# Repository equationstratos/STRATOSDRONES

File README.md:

# STRATOSDRONES

**A fully open-source DJI Tello EDU class drone** — hardware (KiCad PCB you can order assembled from JLCPCB), 3D-printable frame (OpenSCAD), flight firmware (ESP32-P4 + ESP32-C6), Tello SDK 2.0 wire-compatible programming interface, swarming, and a complete Gazebo simulation that speaks the exact same protocol as the real drone.

> Fly your mission scripts against the Gazebo sim today, order the PCB, print the frame, and run the *same unmodified Python code* on the real drone.

## Specs vs DJI Tello EDU

| | DJI Tello EDU | STRATOSDRONES |
|---|---|---|
| Weight / wheelbase | 87 g / 118 mm | ~92 g / 118 mm |
| Motors / props | brushed 8520 / 3" | identical (Tello-compatible props) |
| MCU | proprietary + Myriad 2 | **ESP32-P4** (flight + camera + H.264 hw encoder) + **ESP32-C6** (Wi-Fi 6) |
| Sensors | IMU, baro, ToF, optical flow | ICM-42688-P, SPL06-001, VL53L1X, PMW3901 |
| Camera | 5 MP, 720p30 H.264 | **OV5647 5 MP MIPI-CSI, hardware H.264 720p30 (Tello wire format) + 1080p30 extension** |
| SDK | Tello SDK 2.0 (UDP 8889/8890/11111) | **wire-compatible incl. video** — [djitellopy](https://github.com/damiafuentes/DJITelloPy) works unmodified — plus extensions |
| Swarm | STA mode on shared AP | identical, **plus simulated swarms in Gazebo** |
| Simulation | none | full Gazebo Harmonic model running the *same* flight-control code |
| License | closed | MIT (code), CERN-OHL-P-2.0 (hardware), CC-BY-4.0 (docs) |

## Repository layout

```
fc_core/            Platform-independent flight control core (pure C99, no RTOS deps)
                    — compiled into BOTH the ESP32-P4 firmware and the Gazebo plugin
firmware/           ESP-IDF project for ESP32-P4 (esp32p4 target)
sim/                Gazebo Harmonic plugin, drone SDF model, worlds, swarm launcher
sim/viz/            Self-contained 3-D drone viewer (open drone_viewer.html) generated from the SDF
sdk/python/         stratospy: thin djitellopy add-on for STRATOS extensions + examples
android/            Android ground-control app (Tello SDK 2.0 client — takeoff/land/flip, joysticks, live video)
fr4n6/              Fr4n6-001 — the 5" brushless FPV-class model (charter, CAD, hardware plan; same fc_core)
foldable/           Fr4n7-F — folding-arm variant (spring pivots + latch; button or `deploy`-servo release; CAD + animated viewer)
fpv85/              Fr4n8-001 — outdoor micro FPV, 85 mm class (ELRS radio + analog 5.8G video, 2S brushless; CAD + viewer + playground sim)
fpv2/               Fr4n9-001 — outdoor 2" FPV, 98 mm (same design language + SAME shared AIO board as fpv85)
TinyHoopMK1/        Fr4n10-001 — programmable/swarm 2.5" FPV (JeNo Pocket V2 frame, clean-room): 4 modes (manual/stabilized/program/swarm), ELRS + LoRa 868 fleet link, flow+ToF position hold, analog or DJI O4 Lite video
hardware/pcb/       KiCad project + JLCPCB fab outputs (gerbers, BOM, CPL) + component map
hardware/pcb_fpv/   STRATOS FPV AIO — shared brushless 2S board for fpv85+fpv2 (design.py → CI-generated KiCad board)
hardware/pcb_tinyhoop/ STRATOS TINYHOOP AIO — the TinyHoop MK1 board (FPV AIO + flow/ToF + SX1262 LoRa + GPS, 2S-3S)
sdk/lora_dongle/    ground LoRa dongle (ESP32+SX1262) — transparent fc_lorap bridge for the no-Wi-Fi PC/fleet link
hardware/frame/     Parametric OpenSCAD frames → STL:
                      • frame.scad …        open racing-style X-frame
                      • tello_style/ …      closed Tello-size clamshell body
docs/               Build guide, bring-up, SDK reference, architecture, safety
oasis30/            OASIS 30 — 3" build on the Sub250 OasisFly30 frame: parametric
                    gmsh-OCC model (STEP + printable STL), the printed parts the kit
                    lacks, 3-D viewer + assembly simulator
atelier/            FPV build-workshop site + print posters (buy-the-drone option, FPV league)
```

## Quick start (simulation)

```bash
# Ubuntu 24.04 — install Gazebo Harmonic (see docs/build_guide.md), then:
cd sim && cmake -B build && cmake --build build
./spawn_swarm.sh 1                      # one simulated drone on 127.0.0.2

pip install djitellopy
python sdk/python/examples/01_hover.py  # takeoff → hover → land, via the Tello protocol
python sdk/python/examples/03_swarm.py  # ./spawn_swarm.sh 3 first
```

## Status

- [x] `fc_core` flight control core + host tests (ctest, closed-loop SIL)
- [x] Gazebo Harmonic model + plugin, Tello-protocol UDP endpoint, multi-drone
- [x] Python SDK layer + examples
- [x] KiCad PCB + JLCPCB fab package *(review in KiCad before ordering — see docs/build_guide.md)*
- [x] OpenSCAD frame → STL
- [x] ESP32-P4 firmware tree (flight task, drivers, SDK server, H.264 video)
- [x] TinyHoop MK1 (Fr4n10): 4-mode manager + show/figure executor + CRSF + LoRa protocol in `fc_core` (host-tested); DShot/CRSF/SX1262/LoRa firmware (CI-compiled); STRATOS TINYHOOP AIO board; clean-room JeNo Pocket V2 CAD (STL+DXF); `stratospy.lora` + choreography compiler
- [ ] Hardware bring-up (waiting on first PCB batch — see docs/bringup.md)
- [ ] Real-world flight tuning, camera pipeline validation, 2-drone swarm

## Safety

This is a flying machine with spinning propellers. Read `docs/safety.md` before the first
flight: prop guards on, props off for the first power-up, never hand-catch, lipo handling.

## Licenses

- Code (fc_core, firmware, sim, sdk): [MIT](LICENSE)
- Hardware (hardware/): [CERN-OHL-P-2.0](LICENSES/CERN-OHL-P-2.0.txt)
- Documentation (docs/): [CC-BY-4.0](LICENSES/CC-BY-4.0.txt)

Clean-room policy: Crazyflie / ESP-Drone / Betaflight are used as *algorithmic references
only* (papers, datasheets, published behavior). No GPL code is copied. See CONTRIBUTING.md.

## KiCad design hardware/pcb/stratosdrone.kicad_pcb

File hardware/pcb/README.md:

# STRATOSDRONE PCB

A 4-layer, **36×70 mm Tello-style portrait** controller board for the
STRATOSDRONE: chip-down ESP32-P4 (flight + camera + hardware H.264) with an
ESP32-C6-MINI-1 Wi-Fi co-processor, IMU / barometer / ToF / optical-flow
sensors, a MIPI-CSI camera FFC at the nose, 1S USB-C charging at the rear, and
four corner brushed-motor drivers. It drops into the printed body pod
(`../frame/tello_style/`).

**Lost among the parts?** See the annotated component map (`make map`):

**See the board populated in 3-D** — open [`viz/pcb3d_viewer.html`](viz/) (one
offline file, double-click). It synthesises a clean 3-D body for every one of the
115 components straight from the placement data, so the board renders fully
populated **without needing KiCad's 3-D models** (which aren't installed here).
Top / bottom / copper / silkscreen / logo, hover to inspect any part. See
[`viz/README.md`](viz/README.md).

> **Read [`KNOWN_GAPS.md`](KNOWN_GAPS.md) before ordering.** This design is
> generated as a reviewable starting point: the netlist, BOM and placement are
> complete and self-consistent, but signal routing and several datasheet-level
> verifications must be finished by hand in KiCad first.

## Design as code

The board is generated from one source of truth, `scripts/design.py`
(components, LCSC parts, pin-level nets, placement). Regenerate everything:

```bash
make            # board + pinmap + fab + consistency check
make board      # stratosdrone.kicad_pcb from design.py
make pinmap     # firmware/components/board/include/board_pinmap.h
make fab        # jlcpcb/bom.csv, cpl.csv, gerbers/ (preliminary)
make check      # assert board nets + firmware pinmap match design.py
make preview    # preview/top.svg, bottom.svg
```

Requires KiCad 7 (`pcbnew` Python module + `kicad-cli`). The vendored
Espressif P4/C6 symbols and footprints in `lib/` were downgraded to the
KiCad 7 file format; `lib/strat.pretty/` holds project-specific footprints.

## Files

```
stratosdrone.kicad_pcb   generated board (open in KiCad to route)
scripts/design.py        ← edit this; the authoritative netlist + BOM
scripts/gen_pcb.py       design.py -> .kicad_pcb (place, net, pour)
scripts/gen_pinmap.py    design.py -> firmware board_pinmap.h
scripts/export_fab.py    -> jlcpcb/{bom.csv,cpl.csv,gerbers/}
scripts/check_consistency.py  CI gate: board == design == firmware pinmap
lib/                     vendored Espressif + project footprints/symbols
jlcpcb/                  fabrication outputs (BOM/CPL real; gerbers preliminary)
```

## Ordering at JLCPCB (after routing + review)

1. Finish routing in KiCad, fill zones (**B**), run **DRC** to zero errors.
2. Re-export gerbers/drill from KiCad (Plot) — *not* from `export_fab.py`,
   which exports the unrouted board.
3. PCB options: **4-layer**, 1.6 mm, JLC04161H-7628 stackup (controlled
   impedance for the USB/CSI pairs), 0.5 oz outer / 0.5 oz inner, ENIG finish
   (recommended for the fine-pitch QFN and FFC pads).
4. Assembly: **PCBA**, both sides (top: MCU/power/most parts; bottom: the two
   downward sensors). Upload `jlcpcb/bom.csv` and `jlcpcb/cpl.csv`; they use
   the JLC column format and the LCSC part numbers from `design.py`.
5. Confirm every **VERIFY** item in `KNOWN_GAPS.md` is closed.

## Approx. cost (qty 5, indicative — get a live quote)

| | per board |
|---|---|
| 4-layer PCB + PCBA (qty 5, both sides) | ~$18–28 |
| ICM-42688-P (the expensive line) | ~$10.5 |
| ESP32-P4 + C6 module + flash | ~$9 |
| sensors (baro, ToF, flow) + camera module | ~$11 |
| passives, connectors, FETs, USB-C, regulators | ~$6 |
| **board total** | **~$55–65** |
| + motors (×4), 1S 1100 mAh pack, props, frame filament | ~$25 |

Estimate only — not a quote, and excludes the verification rework above.

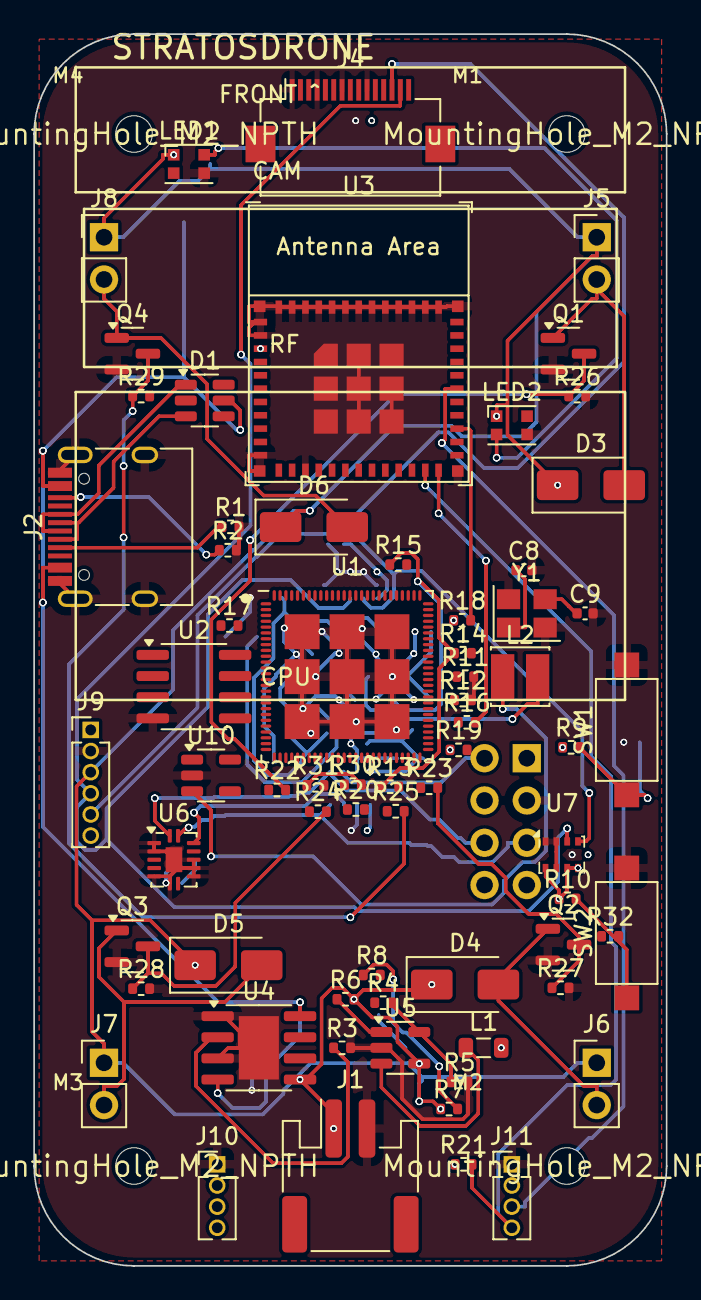
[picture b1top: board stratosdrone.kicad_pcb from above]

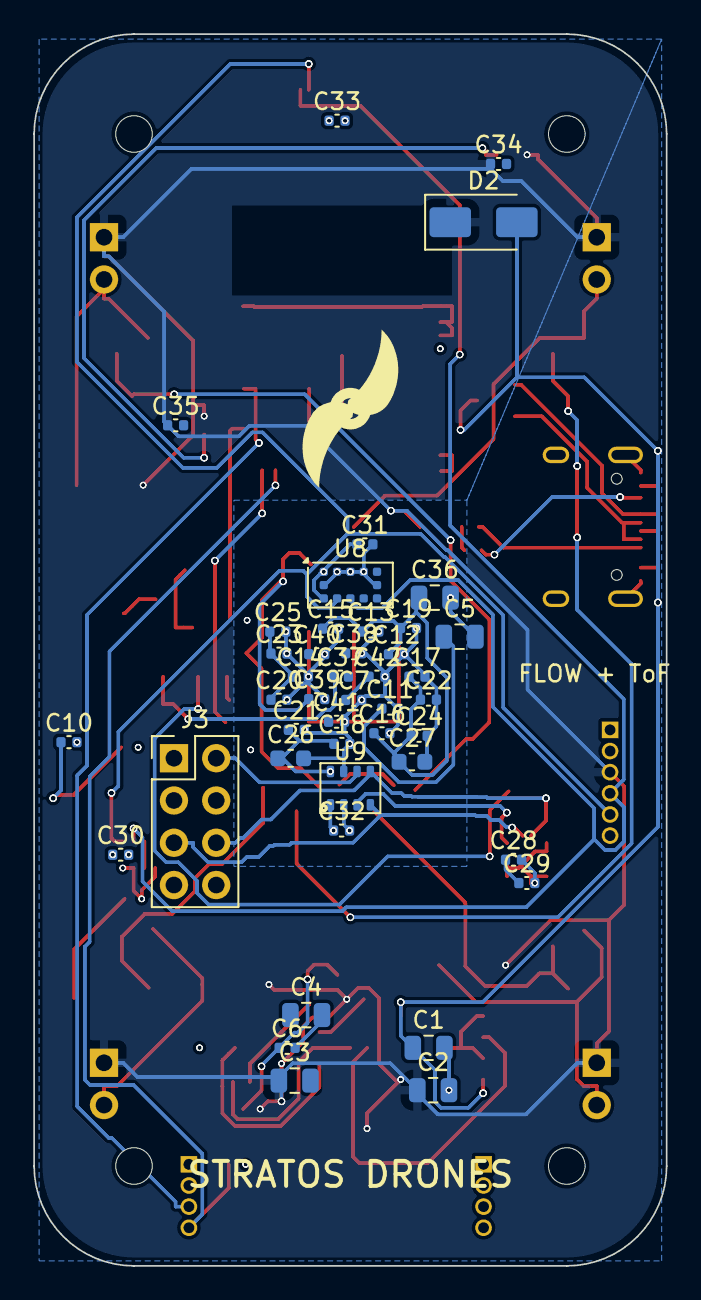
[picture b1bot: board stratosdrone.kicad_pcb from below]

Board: 4 copper layers, 38.0 x 74.0 mm, 116 parts (44 on the bottom side), 78 nets.

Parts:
C1, C2, C3, C36: 10uF; C_0805_2012Metric
C4, C5: 22uF; C_0805_2012Metric
C6, C11, C12, C13, C14, C15, C16, C17, C18, C19, C20, C21, C22, C23, C24, C25, C28, C29, C30, C31, C32, C34, C35, C39, C41, C42: 100nF; C_0402_1005Metric
C7, C10, C33, C38, C40: 1uF; C_0402_1005Metric
C8, C9: 10pF; C_0402_1005Metric
C26, C27: 10uF; C_0603_1608Metric
C37: 20pF; C_0402_1005Metric
D1: USBLC6-2SC6; SOT-23-6
D2: SS34-DNP; D_SMA
D3, D4, D5, D6: SS34; D_SMA
J1: BATT_PH2; JST_PH_S2B-PH-SM4-TB_1x02-1MP_P2.00mm_Horizontal
J2: USB-C-16P; USB_C_Receptacle_HRO_TYPE-C-31-M-12
J3: FLOW_HDR; PinHeader_2x04_P2.54mm_Vertical
J4: CAM_FFC15; Hirose_FH12-15S-0.5SH_1x15-1MP_P0.50mm_Horizontal
J5: MOTOR1; PinHeader_1x02_P2.54mm_Vertical
J6: MOTOR2; PinHeader_1x02_P2.54mm_Vertical
J7: MOTOR3; PinHeader_1x02_P2.54mm_Vertical
J8: MOTOR4; PinHeader_1x02_P2.54mm_Vertical
J9: EXP; PinHeader_1x06_P1.27mm_Vertical
J10: DBG; PinHeader_1x04_P1.27mm_Vertical
J11: C6DBG; PinHeader_1x04_P1.27mm_Vertical
L1: 10uH; L_0805_2012Metric
L2: 2.2uH; L_Cenker_CKCS3015
LED1, LED2: WS2812B-2020; LED_WS2812B-2020_PLCC4_2.0x2.0mm
MH1, MH2, MH3, MH4: MountingHole_M2_NPTH; MountingHole_2.2mm_M2
Q1, Q2, Q3, Q4: AO3400A; SOT-23
R1, R2: 5.1k; R_0402_1005Metric
R3: 1.2k; R_0402_1005Metric
R4, R30, R31: 453k; R_0402_1005Metric
R5, R6, R7, R8, R26, R27, R28, R29: 100k; R_0402_1005Metric
R9, R10, R13, R14, R15, R21, R32: 10k; R_0402_1005Metric
R11, R12: 4.02k; R_0402_1005Metric
R16, R17, R18, R19, R20: 51k; R_0402_1005Metric
R22, R23, R24, R25: 100R; R_0402_1005Metric
SW1: RESET; SW_SPST_CK_RS282G05A3
SW2: BOOT; SW_SPST_CK_RS282G05A3
U1: ESP32-P4NRW32; ESP32-P4
U2: W25Q128JVSIQ; SOIC-8_3.9x4.9mm_P1.27mm
U3: ESP32-C6-MINI-1
U4: TP4056-42-ESOP8; SOIC-8-1EP_3.9x4.9mm_P1.27mm_EP2.41x3.81mm
U5: SY8089AAAC; SOT-23-5
U6: ICM-42688-P; DHVQFN-14-1EP_2.5x3mm_P0.5mm_EP1x1.5mm
U7: SPL06-001; Bosch_LGA-8_2x2.5mm_P0.65mm_ClockwisePinNumbering
U8: VL53L1X; ST_VL53L1x
U9: PMW3901MB; PMW3901MB-TXQT
U10: TLV62569DBVR; SOT-23-5
Y1: 40MHz; Crystal_SMD_3225-4Pin_3.2x2.5mm

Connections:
3V3: C4.1, C12.1, C13.1, C14.1, C15.1, C16.1, C17.1, C18.1, C19.1, C20.1, C21.1, C22.1, C23.1, C24.1, C25.1, C26.1, C27.1, C28.1, C29.1, C30.1, C31.1, C32.1, C33.1, C36.1, J3.1, J3.8, J4.15, J9.1, J10.4, L1.2, R4.1, R9.1, R10.1, R16.1, R17.1, R18.1, R19.1, R20.1, R21.1, R32.1, U1.9, U1.21, U1.51, U1.62, U1.75, U1.77, U1.85, U1.96, U1.101, U1.102, U3.3, U6.5, U6.8, U7.5, U7.6, U7.8, U8.1, U8.11, U9.1, U9.8, U10.4
3V3_EN: R6.1, U5.1
BOOT: R10.2, SW2.1, U1.66
C6_BOOT: J11.4, R21.2, U3.23
C6_EN: U1.98, U3.8
C6_U0RXD: J11.3, U3.30
C6_U0TXD: J11.2, U3.31
CAM_PWDN: J4.11, U1.53
CC1: J2.A5, R1.1
CC2: J2.B5, R2.1
CHIP_PU: C10.1, R9.2, SW1.1, U1.103
CSI_CKN: J4.8, U1.45
CSI_CKP: J4.9, U1.44
CSI_D0N: J4.2, U1.42
CSI_D0P: J4.3, U1.43
CSI_D1N: J4.5, U1.46
CSI_D1P: J4.6, U1.47
CSI_REXT: R11.1, U1.48
CS_FLOW: J3.2, U1.14, U9.6
CS_IMU: U1.13, U6.12
DSI_REXT: R12.1, U1.34
EN_DCDC: U1.79, U10.1
EXP_IO: J9.6, U1.24
FB3V3: R4.2, R5.1, U5.5
FB_DCDC: C37.2, R30.2, R31.1, U1.78, U10.5
FLASH_CK: U1.32, U2.6
FLASH_CS: R13.2, U1.27, U2.1
FLASH_IO0: U1.33, U2.5
FLASH_IO1: U1.28, U2.2
FLASH_IO2: R14.2, U1.29, U2.3
FLASH_IO3: R15.2, U1.31, U2.7
GND: C1.2, C2.2, C3.2, C4.2, C5.2, C6.2, C7.2, C8.2, C9.2, C10.2, C11.2, C12.2, C13.2, C14.2, C15.2, C16.2, C17.2, C18.2, C19.2, C20.2, C21.2, C22.2, C23.2, C24.2, C25.2, C26.2, C27.2, C28.2, C29.2, C30.2, C31.2, C32.2, C33.2, C34.2, C35.2, C36.2, C38.2, C39.2, C40.2, C41.2, C42.2, D1.2, J1.2, J2.A1, J2.A12, J2.B1, J2.B12, J2.S1, J3.3, J3.7, J4.1, J4.4, J4.7, J4.10, J9.2, J10.1, J11.1, LED1.3, LED2.3, Q1.2, Q2.2, Q3.2, Q4.2, R1.2, R2.2, R3.2, R5.2, R8.2, R11.2, R12.2, R26.2, R27.2, R28.2, R29.2, R31.2, SW1.2, SW2.2, U1.105, U2.4, U3.1, U3.2, U3.11, U3.14, U3.36, U3.37, U3.38, U3.39, U3.40, U3.41, U3.42, U3.43, U3.44, U3.45, U3.46, U3.47, U3.48, U3.49, U3.50, U3.51, U3.52, U3.53, U4.1, U4.3, U4.9, U5.2, U6.2, U6.3, U6.6, U6.7, U6.9, U6.10, U6.11, U6.15, U7.1, U7.2, U7.7, U8.2, U8.3, U8.4, U8.6, U8.12, U9.2, U9.7, U10.2, Y1.2, Y1.4
GPIO36_STRAP: R32.2, U1.68
I2C_SCL: J4.13, J9.5, U1.8, U7.4, U8.10
I2C_SDA: J4.14, J9.4, U1.7, U7.3, U8.9
IMU_INT: U1.23, U6.4
LED_D12: LED1.4, LED2.2
LED_DIN: LED1.2, U1.52
M1_D: D3.2, J5.2, Q1.1
M1_G: R22.1, U1.87
M1_GATE: Q1.3, R22.2, R26.1
M2_D: D4.2, J6.2, Q2.1
M2_G: R23.1, U1.88
M2_GATE: Q2.3, R23.2, R27.1
M3_D: D5.2, J7.2, Q3.1
M3_G: R24.1, U1.89
M3_GATE: Q3.3, R24.2, R28.1
M4_D: D6.2, J8.2, Q4.1
M4_G: R25.1, U1.90
M4_GATE: Q4.3, R25.2, R29.1
PROG: R3.1, U4.2
SDIO_CLK: U1.19, U3.25
SDIO_CMD: R16.2, U1.20, U3.24
SDIO_D0: R17.2, U1.15, U3.26
SDIO_D1: R18.2, U1.16, U3.27
SDIO_D2: R19.2, U1.17, U3.28
SDIO_D3: R20.2, U1.18, U3.29
SPI_MISO: J3.6, U1.12, U6.1, U9.5
SPI_MOSI: J3.5, U1.11, U6.14, U9.4
SPI_SCLK: J3.4, U1.10, U6.13, U9.3
SW3V3: L1.1, U5.3
SW_CORE: L2.1, U10.3
U0RXD: J10.3, U1.70
U0TXD: J10.2, U1.69
USB_DM_C: D1.3, J2.A7, J2.B7
USB_DM_MCU: D1.4, U1.49
USB_DP_C: D1.1, J2.A6, J2.B6
USB_DP_MCU: D1.6, U1.50
VBAT: C2.1, C3.1, C34.1, C35.1, D2.1, D3.1, D4.1, D5.1, D6.1, J1.1, J5.1, J6.1, J7.1, J8.1, J9.3, LED1.1, LED2.1, R6.2, R7.1, U4.5, U5.4
VBAT_SENSE: C6.1, R7.2, R8.1, U1.22
VBUS: C1.1, D1.5, D2.2, J2.A4, J2.A9, J2.B4, J2.B9, U4.4, U4.8
VDD_CORE: C5.1, C11.1, C37.1, L2.2, R30.1, U1.26, U1.76, U1.91
VDD_FLASHIO: C38.1, C39.1, R13.1, R14.1, R15.1, U1.30, U1.71, U2.8
VDD_MIPI: C7.1, C42.1, U1.41, U1.73
VDD_PSRAM: C40.1, C41.1, U1.59, U1.67, U1.72
VL53_XSHUT: U1.25, U8.5
XTAL_N: C9.1, U1.99, Y1.3
XTAL_P: C8.1, U1.100, Y1.1

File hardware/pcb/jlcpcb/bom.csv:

Comment,Designator,Footprint,LCSC Part #
1.2k,R3,R_0402_1005Metric,C4180
100R,"R22,R23,R24,R25",R_0402_1005Metric,C25092
100k,"R5,R6,R7,R8,R26,R27,R28,R29",R_0402_1005Metric,C25741
100nF,"C6,C11,C12,C13,C14,C15,C16,C17,C18,C19,C20,C21,C22,C23,C24,C25,C28,C29,C30,C31,C32,C34,C35,C39,C41,C42",C_0402_1005Metric,C1525
10k,"R9,R10,R13,R14,R15,R21,R32",R_0402_1005Metric,C25744
10pF,"C8,C9",C_0402_1005Metric,C1555
10uF,"C1,C2,C3,C36",C_0805_2012Metric,C15850
10uF,"C26,C27",C_0603_1608Metric,C19702
10uH,L1,L_0805_2012Metric,C408412
1uF,"C7,C10,C33,C38,C40",C_0402_1005Metric,C52923
2.2uH,L2,L_Cenker_CKCS3015,C43389
20pF,C37,C_0402_1005Metric,C1554
22uF,"C4,C5",C_0805_2012Metric,C45783
4.02k,"R11,R12",R_0402_1005Metric,C25752
40MHz,Y1,Crystal_SMD_3225-4Pin_3.2x2.5mm,C2831465
453k,"R4,R30,R31",R_0402_1005Metric,C123734
5.1k,"R1,R2",R_0402_1005Metric,C25905
51k,"R16,R17,R18,R19,R20",R_0402_1005Metric,C25905
AO3400A,"Q1,Q2,Q3,Q4",SOT-23,C20917
BATT_PH2,J1,JST_PH_S2B-PH-SM4-TB_1x02-1MP_P2.00mm_Horizontal,C160404
BOOT,SW2,SW_SPST_CK_RS282G05A3,C720477
CAM_FFC15,J4,Hirose_FH12-15S-0.5SH_1x15-1MP_P0.50mm_Horizontal,C2884418
ESP32-C6-MINI-1,U3,ESP32-C6-MINI-1,C3013606
ESP32-P4NRW32,U1,ESP32-P4,C22387510
ICM-42688-P,U6,DHVQFN-14-1EP_2.5x3mm_P0.5mm_EP1x1.5mm,C2840095
PMW3901MB,U9,PMW3901MB-TXQT,C2920328
RESET,SW1,SW_SPST_CK_RS282G05A3,C720477
SPL06-001,U7,Bosch_LGA-8_2x2.5mm_P0.65mm_ClockwisePinNumbering,C2684428
SS34,"D3,D4,D5,D6",D_SMA,C8678
SY8089AAAC,U5,SOT-23-5,C78988
TLV62569DBVR,U10,SOT-23-5,C141836
TP4056-42-ESOP8,U4,SOIC-8-1EP_3.9x4.9mm_P1.27mm_EP2.41x3.81mm,C16581
USB-C-16P,J2,USB_C_Receptacle_HRO_TYPE-C-31-M-12,C165948
USBLC6-2SC6,D1,SOT-23-6,C7519
VL53L1X,U8,ST_VL53L1x,C2970716
W25Q128JVSIQ,U2,SOIC-8_3.9x4.9mm_P1.27mm,C97521
WS2812B-2020,"LED1,LED2",LED_WS2812B-2020_PLCC4_2.0x2.0mm,C965555

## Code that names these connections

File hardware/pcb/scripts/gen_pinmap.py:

#!/usr/bin/env python3
"""Generate firmware/components/board/include/board_pinmap.h from design.py.

The PCB net assignment and the firmware GPIO macros must never drift apart.
design.PINMAP is the single source; this emits the C header the firmware
compiles against. Run after changing PINMAP, and commit both.
"""
import os
import sys

HERE = os.path.dirname(os.path.abspath(__file__))
REPO = os.path.dirname(os.path.dirname(os.path.dirname(HERE)))
OUT = os.path.join(REPO, "firmware", "components", "board", "include", "board_pinmap.h")

sys.path.insert(0, HERE)
import design  # noqa: E402


def gpio_num(sig):
    # "GPIO45" -> 45
    return int(sig.replace("GPIO", ""))


def main():
    p = design.PINMAP
    lines = [
        "/* board_pinmap.h — GENERATED by hardware/pcb/scripts/gen_pinmap.py.",
        " * Mirrors the PCB net assignment (design.py PINMAP) for ESP32-P4 rev A.",
        " * Do not edit by hand; edit design.py and re-run the generator.",
        " * SPDX-License-Identifier: MIT */",
        "#ifndef BOARD_PINMAP_H",
        "#define BOARD_PINMAP_H",
        "",
        "/* SPI bus (ICM-42688-P + PMW3901) */",
        f"#define PIN_SPI_SCLK   {gpio_num(p['SPI_SCLK'])}",
        f"#define PIN_SPI_MOSI   {gpio_num(p['SPI_MOSI'])}",
        f"#define PIN_SPI_MISO   {gpio_num(p['SPI_MISO'])}",
        f"#define PIN_CS_IMU     {gpio_num(p['CS_IMU'])}",
        f"#define PIN_CS_FLOW    {gpio_num(p['CS_FLOW'])}",
        f"#define PIN_IMU_INT    {gpio_num(p['IMU_INT'])}",
        "",
        "/* I2C bus (SPL06-001 0x76, VL53L1X 0x29, camera SCCB) */",
        f"#define PIN_I2C_SDA    {gpio_num(p['I2C_SDA'])}",
        f"#define PIN_I2C_SCL    {gpio_num(p['I2C_SCL'])}",
        f"#define PIN_VL53_XSHUT {gpio_num(p['VL53_XSHUT'])}",
        "",
        "/* motors (M1 FR, M2 BR, M3 BL, M4 FL — see fc_core mixer) */",
        f"#define PIN_MOTOR_1    {gpio_num(p['MOTOR_1'])}",
        f"#define PIN_MOTOR_2    {gpio_num(p['MOTOR_2'])}",
        f"#define PIN_MOTOR_3    {gpio_num(p['MOTOR_3'])}",
        f"#define PIN_MOTOR_4    {gpio_num(p['MOTOR_4'])}",
        "",
        "/* battery sense: 100k/100k divider (VERIFY ADC unit/channel for GPIO%d) */"
        % gpio_num(p["VBAT_ADC"]),
        f"#define PIN_VBAT_ADC     {gpio_num(p['VBAT_ADC'])}",
        "#define VBAT_ADC_UNIT    ADC_UNIT_1",
        "#define VBAT_ADC_CHANNEL ADC_CHANNEL_4",
        "",
        "/* misc */",
        f"#define PIN_WS2812     {gpio_num(p['WS2812'])}",
        f"#define PIN_CAM_PWDN   {gpio_num(p['CAM_PWDN'])}",
        f"#define PIN_EXP_IO     {gpio_num(p['EXP_IO'])}",
        "",
        "/* SDIO link to ESP32-C6 (esp-hosted) — also set in sdkconfig */",
        f"#define PIN_SDIO_CLK   {gpio_num(p['SDIO_CLK'])}",
        f"#define PIN_SDIO_CMD   {gpio_num(p['SDIO_CMD'])}",
        f"#define PIN_SDIO_D0    {gpio_num(p['SDIO_D0'])}",
        f"#define PIN_SDIO_D1    {gpio_num(p['SDIO_D1'])}",
        f"#define PIN_SDIO_D2    {gpio_num(p['SDIO_D2'])}",
        f"#define PIN_SDIO_D3    {gpio_num(p['SDIO_D3'])}",
        f"#define PIN_C6_EN      {gpio_num(p['C6_EN'])}",
        "",
        "/* UART0 console + BOOT strap (VERIFY against ESP32-P4 datasheet) */",
        f"#define PIN_UART0_TX   {gpio_num(p['UART0_TX'])}",
        f"#define PIN_UART0_RX   {gpio_num(p['UART0_RX'])}",
        f"#define PIN_BOOT_STRAP {gpio_num(p['BOOT_STRAP'])}",
        "",
        "#endif",
        "",
    ]
    with open(OUT, "w") as f:
        f.write("\n".join(lines))
    print(f"wrote {OUT}")


if __name__ == "__main__":
    main()

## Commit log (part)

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2026-06-12 fc_core: platform-independent flight control core with SIL tests
    Pure C99 flight core (Mahony AHRS, 3-state vertical KF, optical-flow
    velocity/position estimator, cascaded PID, X-mixer, Tello-style commander
    and flight state machine) shared verbatim between the ESP32-P4 firmware
    and the Gazebo plugin. Includes a 6-DOF SIL plant and ctest suite: full
    takeoff/hover/go/rotate/rc/land mission passes closed-loop.
    https://claude.ai/code/session_011szEEHZ8KTTsZmGFgY6Cjw
2026-06-12 Tello SDK 2.0 protocol layer, SITL runner, stratospy + mission tests
    fc_sdk: transport-free Tello SDK 2.0 command parser/replies/state packets
    (deferred ok on motion completion, rc/emergency silent, EXT led, video and
    param extensions). sitl_runner: real-time POSIX SITL drone on a loopback
    IP. stratospy: djitellopy add-on (enable_sim, extensions, SITL spawner).
    pytest suite flies full missions and a 3-drone TelloSwarm headlessly with
    unmodified djitellopy.
2026-06-12 Gazebo Harmonic simulation: plugin, model, worlds, swarm, mission tests
    StratosFcSystem (gz-sim8 system plugin) embeds fc_core + the Tello SDK
    server per drone; analytic flow/ToF/baro + noisy IMU from ground truth
    (fully headless, no GPU). Rotor forces mirror the SIL plant so behavior
    matches host tests. SDF model (118 mm / 92 g), hover_test + swarm_3
    worlds (RTF 4), spawn_swarm.sh generator, gz_video_bridge (gz camera ->
    libx264 H.264 Annex-B -> UDP 11111, Tello wire format). pytest flies a
2026-06-12 3D-printable frame: parametric OpenSCAD X-frame, prop guards, canopy
    118 mm wheelbase, 8520 press-fit pockets with wire channels, PMW3901/ToF
    window, M2 PCB standoffs (36 mm pitch), under-slung 1S battery bay,
    Tello-style 270-degree clip-on prop guards, canopy with 10-degree camera
    cradle, vents and LED light pipes. STL exports included; geometry asserts
    echoed for CI.
    https://claude.ai/code/session_011szEEHZ8KTTsZmGFgY6Cjw
2026-06-13 hardware/pcb: ESP32-P4 board generator (placement + nets + power planes)
    Authoritative design database (design.py: 101 components, 79 nets, full
    LCSC BOM keyed to the extracted ESP32-P4 QFN pinout and board_pinmap.h)
    plus gen_pcb.py which builds stratosdrone.kicad_pcb via the pcbnew API:
    105 footprints placed, 420/497 pads net-assigned, GND/3V3/VBAT/GND copper
    pours on In1/In2/B/F. Vendored + format-downgraded Espressif P4/C6
    footprints for KiCad 7; pcbnew-generated PMW3901 placeholder land.
2026-06-13 hardware/pcb: fab export, pinmap+consistency generators, ordering docs
    export_fab.py (JLCPCB bom.csv 34 lines/92 parts, cpl.csv 92 placements,
    preliminary gerbers), gen_pinmap.py (board_pinmap.h from design.py),
    check_consistency.py (board nets == design == firmware pinmap, all green),
    Makefile, top/bottom SVG previews. Honest README ordering guide,
    KNOWN_GAPS.md (routing + datasheet items to close before fab), and
    docs/hardware_verification_ledger.md (verified vs assumed).
2026-06-13 CI workflows + architecture doc; verify fc_core builds for ESP32-P4
    Six GitHub Actions workflows: fc-core (host ctest), firmware (espressif/idf
    v5.4 esp32p4 build with registry access), sim (SITL + headless Gazebo
    missions/swarm via djitellopy), hardware (regen board, consistency check,
    DRC in kicad 8, fab artifacts), cad (OpenSCAD STL + wheelbase assert),
    python (ruff + import). Verified locally that fc_core + fc_sdk compile and
    link for the esp32p4 target (the full firmware additionally needs the
2026-06-13 firmware: fix missing esp_check.h in sensor/output drivers
    Compile-checking the firmware against the real ESP-IDF v5.x esp32p4
    toolchain (managed components stubbed) caught ESP_RETURN_ON_ERROR used
    without esp_check.h in buses/spl06/vl53l1x/outputs. fc_core + fc_sdk link
    to an esp32p4 image; all six sensor/output drivers now compile clean.
    Added docs: sdk_reference.md, safety.md.
2026-06-13 docs: build guide and hardware bring-up procedure
    build_guide.md (sim-first workflow → order PCB → print frame → assemble)
    and bringup.md (flash P4 + C6, props-off motor checks, sensor calibration,
    first hover, troubleshooting). Cross-references the safety and SDK docs.
2026-06-13 Add Tello-style closed body + reshape PCB to Tello-style + component map
    CAD: hardware/frame/tello_style/ — closed clamshell body in the DJI Tello
    size class (98x92.5mm, 118mm wheelbase, 3in props) but distinct (hex motor
    nacelles, faceted vented canopy, chamfered camera nose, slide-in rear
    battery). body_bottom/body_top/assembly .scad + STL + previews. The open
    X-frame stays as the alternative.
    PCB: reshaped from 42x42 square to a 48x54 portrait Tello-style board that
2026-06-14 Reshape to real-Tello-mainboard style: narrow portrait PCB + elongated body + sim
    Following the reference Tello photos:
    PCB: from 48x54 to a narrow PORTRAIT 32x66 mm board like the real Tello
    mainboard — camera FFC at the nose, ESP32-C6 (RF) + ESP32-P4 (CPU) in
    silkscreen shield zones down the spine, the two downward sensors on the
    bottom, motor pads M1-M4 at the four corners, USB-C on the left side edge,
    battery at the rear. Added Tello-style silkscreen (shield outlines, CAM/RF/
2026-06-14 PCB: real anchor-based placement (decoupling rings the P4) — zero overlaps
    Replaced the naive auto-flow with a proper placer in gen_pcb.py:
    - anchor_map(): each passive is associated with the part it serves, via its
    most-specific shared net (XTAL caps -> crystal, gate R/flyback -> their FET,
    flash pull-ups -> flash, ...) plus overrides for regulator/bulk/decoupling.
    - collision-avoidance find_slot(): clusters each passive tight to its anchor
    via fine expanding rings, with a full-board grid fallback; mounting holes
2026-06-16 hardware/cad: parametric whoop airframe + whoop-look sim visuals
    Primary 3D-printable airframe redesign matching the pushed concept brief: a
    clean swept "whoop" body, removable Tello-style canopy, and a rear slide-in 1S
    battery, around the unchanged electronics (compact 36x70 mainboard, brushed
    8520 motors, 3" props, 118 mm wheelbase).
    hardware/frame/whoop/ (new, parametric OpenSCAD):
    - params.scad: shared functional envelope + a single `guard` variant switch
2026-06-16 site: add static project presentation page + GitHub Pages deploy
    A single-page, dependency-free presentation of STRATOSDRONE (no build step):
    hero, specs vs the DJI Tello EDU, the swept whoop design, the three protection
    variants (none/ring/duct), a "how it's built" breakdown of the five layers, a
    build/order walkthrough, and a lightbox gallery.
    - site/index.html, site/style.css: dark, minimal, aggressive theme.
    - site/assets/: concept brief (resized from g/) + OpenSCAD whoop renders
2026-06-16 site: dark studio renders for the canopy + airframe cards
    The "Designed for the air" section paired a canopy-less, raw OpenSCAD-blue
    frame render with "Removable canopy" copy. Replace it with proper dark studio
    renders that match the rest of the gallery:
    - assembly.scad: add a `show` param ("all" | "frame" | "canopy"); default
    "all" keeps the existing output byte-for-byte.
    - preview/frame.png, preview/canopy.png: dark studio renders (Tomorrow
2026-06-16 pcb: fix VL53L1X (U8) — correct footprint + datasheet pinout
    The ToF sensor was on the wrong footprint (OptoDevice:ST_VL53L0X) with a
    pad map to match, leaving supply and I2C pins on the wrong pads. Moved U8 to
    KiCad's official Sensor_Distance:ST_VL53L1x land and rewired pad-by-pad to the
    ST VL53L1X datasheet:
    1 AVDDVCSEL=3V3 2 AVSSVCSEL=GND 3/4/6/12 GND 5 XSHUT
    7 GPIO1=INT 8 DNC (floating) 9 SDA 10 SCL 11 AVDD=3V3
2026-06-16 pcb: fix TP4056 (U4) charger pinout — STDBY/CE were miswired
    Pin 6 (STDBY, open-collector status) was shorted straight to VBAT
    instead of being wired as the status output, and pin 8 (CE, enable
    input) was aliased to STDBY_N instead of being driven at all. Both
    are real electrical bugs, not just unverified guesses.
    Re-verified the full 8-pin + EP map against the Nanjing Top Power
    TP4056-42-ESOP8 datasheet pin table and cross-checked against an
2026-06-16 hardware/pcb: fix critical ICM-42688-P (U6) pinout — both power pins were grounded
    The previous map tied VDDIO (real pin 5) and VDD (real pin 8) to GND, so the
    IMU could never power up, and wired the host SPI signals to reserved/no-connect
    pads instead of the chip's real AP_CS/AP_SCLK/AP_SDI pins (12/13/14).
    Re-verified the full 14-pin LGA pinout against the TDK InvenSense DS-000347
    pin table and an independent, manufacturer-tagged KiCad symbol, then rewired
    every pad accordingly. Pad-level mapping confirmed via pcbnew after
2026-06-16 hardware/pcb: fix critical SPL06-001 (U7) pinout — VDDIO grounded, SDA shorted
    Same severity class as the U6 fix: the previous map tied real pin 6 (VDDIO)
    to GND, hard-wired real pin 3 (SDA) straight to 3V3, and routed the host's
    I2C_SDA net to real pin 1 (GND) -- shorting the shared I2C bus to ground
    through this chip, which would have affected every other device on the bus.
    Re-verified pad-by-pad against iNavFlight/hardware's SPL06 reference design,
    which uses the identical official KiCad footprint. Pad-level mapping
2026-06-17 hardware/pcb: verify SY8089 (U5) pinout, fix L1 inductor value mismatch
    U5 SOT-23-5 pinout confirmed correct against the Silergy application note
    (no change). L1 was labeled 2.2uH but its LCSC part (C408412) is actually a
    10uH Sunlord MWSA0503S-100MT -- JLCPCB assembly stuffs the part the LCSC
    code resolves to regardless of the printed value, so corrected the value
    field to match reality. Also corrected a stale KNOWN_GAPS note: the FB
    divider computes to 3.318V, not the previously-claimed 3.42V.
2026-06-17 hardware/pcb: add ESP32-P4 core DC-DC (was chip-fatal: core on 3V3, no buck)
    The P4 VDD_HP core rail was tied straight to 3V3 (~2.75x overvoltage =
    instant dead chip), EN_DCDC was hard-tied to 3V3, and there was no actual
    DC-DC converter -- L2/C5 were bare passives on a meaningless switch-node net
    and FB_DCDC was shorted onto the output. Implemented the Espressif-verified
    TLV62569 reference circuit (U10 + L2 2.2uH + output/input/feed-forward caps +
    453k/453k feedback divider), per the official ESP32-P4 Hardware Design
2026-06-17 hardware/pcb: fix P4 internal-LDO rails (PSRAM overvoltage, MIPI, flash IO)
    The P4's four internal LDO OUTPUTS (VDDO_FLASH/PSRAM/3/4) were tied to 3V3,
    which fought the regulators and put 3.3V on the 1.95V-max VDD_PSRAM pins
    (would damage the in-package PSRAM). Per the ESP32-P4 schematic checklist and
    the Function-EV-Board reference:
    - VDDO_3 -> VDD_MIPI_DPHY (2.5V, firmware LDO ch3); resolves the MIPI supply
    - VDDO_PSRAM (1.8V) -> VDD_PSRAM_0/1
2026-06-17 Doc: Mark REXT and sensor aperture items as RESOLVED in KNOWN_GAPS
